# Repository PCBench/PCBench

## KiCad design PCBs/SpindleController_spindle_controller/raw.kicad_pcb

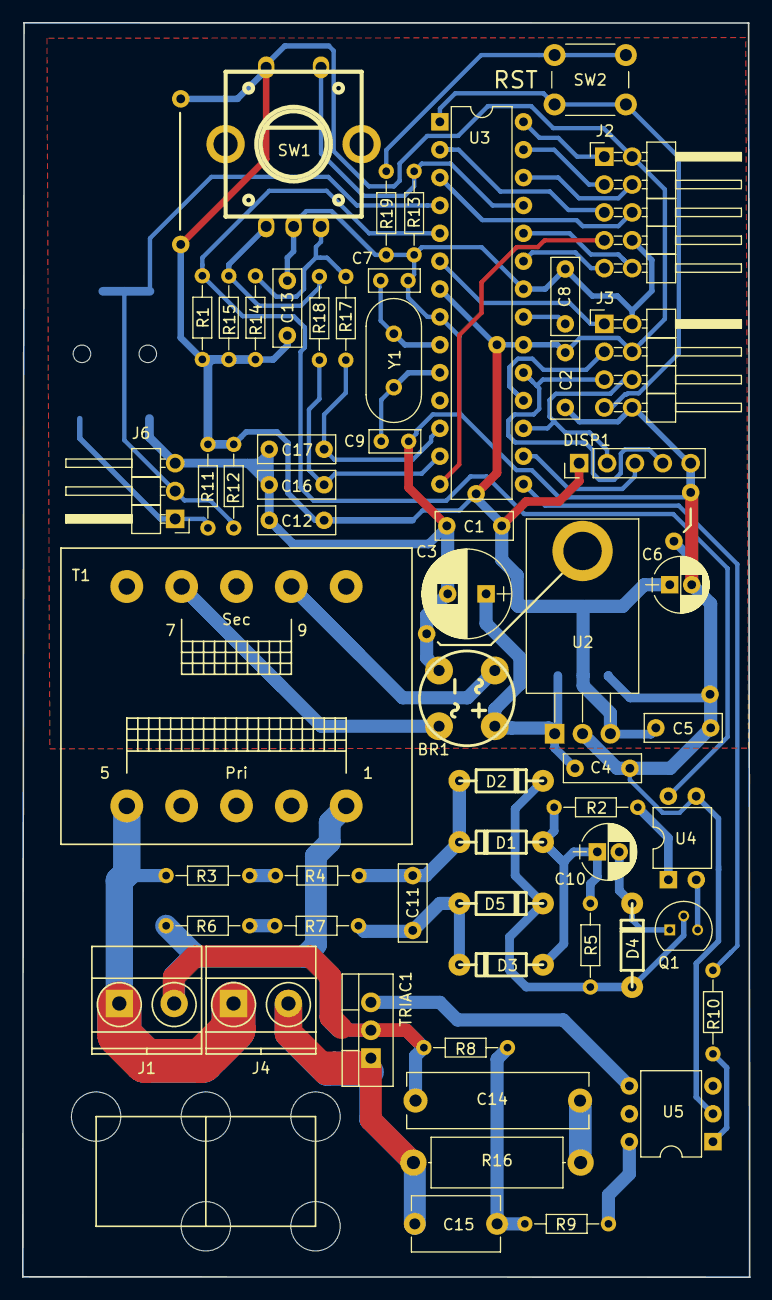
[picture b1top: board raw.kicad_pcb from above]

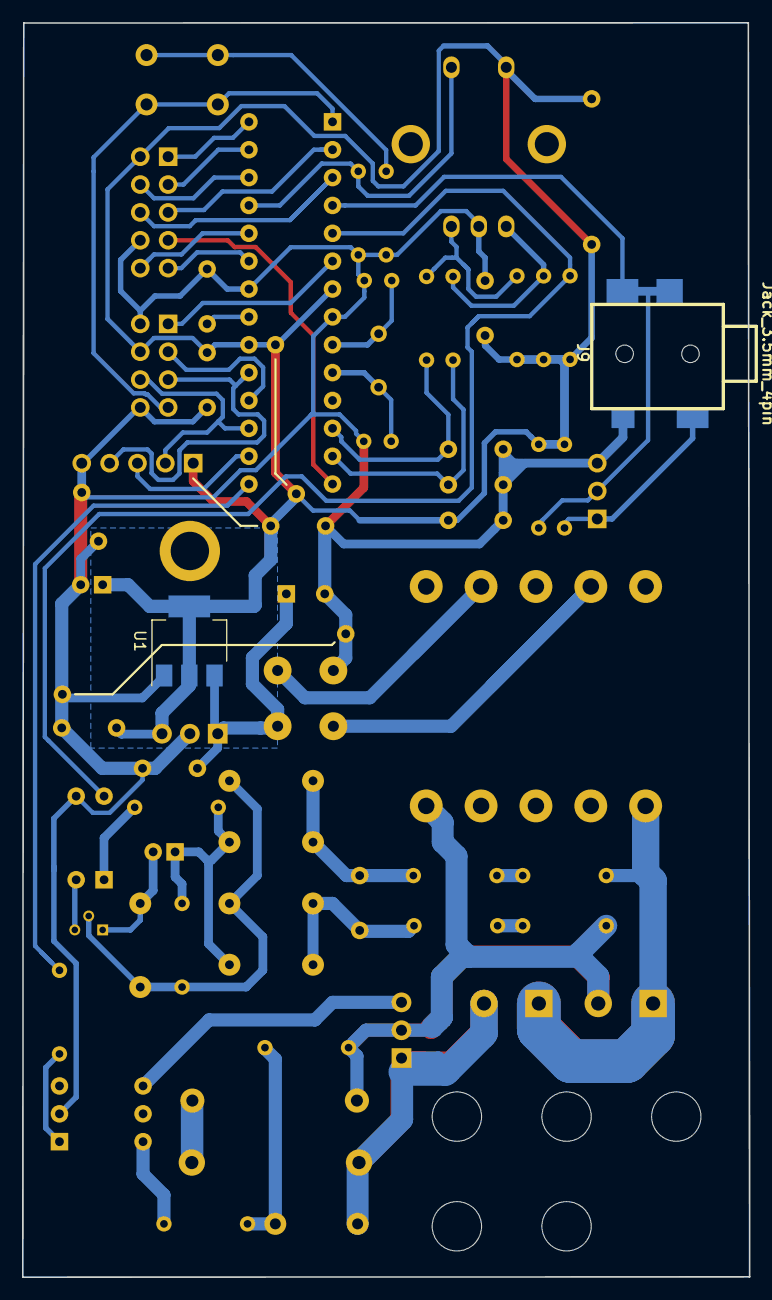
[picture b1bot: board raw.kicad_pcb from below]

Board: 2 copper layers, 66.3 x 114.4 mm, 69 parts (2 on the bottom side), 49 nets.

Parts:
BR1: D_Bridge_+AA-; bridge_wob
C1, C2, C5, C8, C12, C13: 100n; C_Rect_L7.0mm_W2.5mm_P5.00mm
C3: 220u; CP_Radial_D8.0mm_P3.50mm
C4: 470n; C_Rect_L7.0mm_W2.5mm_P5.00mm
C6: 100u; CP_Radial_D5.0mm_P2.00mm
C7, C9: 27p; C_Rect_L4.6mm_W2.0mm_P2.50mm_MKS02_FKP02
C10: 10u; CP_Radial_D5.0mm_P2.00mm
C11: 1n; C_Rect_L7.0mm_W2.5mm_P5.00mm
C14: 10n; C_Rect_L16.5mm_W5.0mm_P15.00mm_MKT
C15: 1n; C_Disc_D8.0mm_W5.0mm_P7.50mm
C16, C17: 47n; C_Rect_L7.0mm_W2.5mm_P5.00mm
D1, D2, D3, D4, D5: 1N4841; diode_do35
DISP1: 8x7SEG; Pin_Header_Straight_1x05_Pitch2.54mm
J1: VAC 230V; TerminalBlock_Pheonix_MKDS1.5-2pol
J2: AUX/CONTROL; Pin_Header_Angled_2x05_Pitch2.54mm
J3: ICP; Pin_Header_Angled_2x04_Pitch2.54mm
J4: Load output; TerminalBlock_Pheonix_MKDS1.5-2pol
J6: CONN_01X03; Pin_Header_Angled_1x03_Pitch2.54mm
J7, J7#2, J7#3, J7#4: GND_JUMPER; JUMPER_PIN
J8, J8#2, J8#3, J8#4: VCC_JUMPER; JUMPER_PIN
J9: Jack_3.5mm_4pin; jack_3.5_sj1-3514-smt
Q1: 2N3904; TO-92_Molded_Narrow
R1, R12, R13, R14, R15: 10k; R_Axial_DIN0204_L3.6mm_D1.6mm_P7.62mm_Horizontal
R2, R10: 1k; R_Axial_DIN0204_L3.6mm_D1.6mm_P7.62mm_Horizontal
R3, R6: 120k; R_Axial_DIN0204_L3.6mm_D1.6mm_P7.62mm_Horizontal
R4, R7: 220k; R_Axial_DIN0204_L3.6mm_D1.6mm_P7.62mm_Horizontal
R5: 33k; R_Axial_DIN0204_L3.6mm_D1.6mm_P7.62mm_Horizontal
R8: 470; R_Axial_DIN0204_L3.6mm_D1.6mm_P7.62mm_Horizontal
R9, R19: 360; R_Axial_DIN0204_L3.6mm_D1.6mm_P7.62mm_Horizontal
R11: 220; R_Axial_DIN0204_L3.6mm_D1.6mm_P7.62mm_Horizontal
R16: 47; R_Axial_DIN0414_L11.9mm_D4.5mm_P15.24mm_Horizontal
R17, R18: 2k2; R_Axial_DIN0204_L3.6mm_D1.6mm_P7.62mm_Horizontal
SW1: Rotary_Encoder_Switch; encoder_alps-ec12d
SW2: SW_SPST; SW_PUSH_6mm
T1: 230 - 6VAC (Spitznagel SPK 01406); Trafo_CHK-EI30-2VA_1xSec
TRIAC1: BT138; TO-220_Vertical
U1: LT1117-5; SOT-223
U2: LM2940CT-5.0; TO-220_Horizontal_connected_tab
U3: ATMEGA328P-PU; DIP-28_W7.62mm
U4: PC817; DIP-4_W7.62mm
U5: MOC3020M; DIP-6_W7.62mm
WIRESTRAP1: 2x Ziplock wire strap; WireStrap_2X_5HOLES
Y1: 16MHz; Crystal_HC49-U_Vertical

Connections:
/DBG: J3.1, U3.6
/MISO: J3.3, U3.18
/MOSI: DISP1.2, J3.6, U3.17
/PB0: J2.7, U3.14
/PC3: J2.4, U3.26
/PD6: J2.9, U3.23
/PD7: J2.10, U3.24
/RENC_A: C16.2, R18.2, U3.13
/RENC_B: C17.2, R17.2, U3.12
/ROT_PULSE: J6.2, J9.2, J9.3, R12.1, U3.4
/RST: J3.7, SW2.1, U3.1
/RX: J2.5, U3.2
/SCK: DISP1.4, J3.5, U3.19
/SCL: J2.1, U3.28
/SDA: J2.3, U3.27
/SEG_CS: DISP1.3, U3.16
/SW1: R13.2, SW1.4, U3.25
/TRIAC_DRIVE: R10.1, U3.15
/TX: J2.6, U3.3
/VAC_L: C14.1, J1.2, R6.2, R8.2, T1.1, TRIAC1.2
/VAC_N: J1.1, J4.1, R3.2, T1.5
/ZCROSS_PULSE: R1.1, U3.5, U4.4
GND: BR1.4, C1.2, C2.1, C3.2, C4.2, C5.2, C6.2, C7.2, C8.2, C9.2, C12.2, C13.1, C16.1, C17.1, DISP1.5, J2.8, J3.2, J3.8, J6.3, J7.1, J7#2.1, J7#3.1, J7#4.1, J9.4, R13.1, R19.2, SW1.2, U1.1, U2.2, U3.8, U3.22, U4.3, U5.2
unnamed: BR1.1, C3.1, C4.1, U1.3, U2.1
unnamed: BR1.2, T1.9
unnamed: BR1.3, T1.7
unnamed: C7.1, U3.9, Y1.1
unnamed: C8.1, U3.21
unnamed: C9.1, U3.10, Y1.2
unnamed: C10.1, D1.1, D3.1, R2.2, R5.2
unnamed: C10.2, D4.2, Q1.1
unnamed: C11.1, D1.2, D2.1, R4.1
unnamed: C11.2, D3.2, D5.1, R7.1
unnamed: C14.2, R16.2
unnamed: C15.1, R8.1, R9.2
unnamed: C15.2, J4.2, R16.1, TRIAC1.1
unnamed: D2.2, D4.1, D5.2, Q1.2, R5.1
unnamed: J6.1, J9.1, R11.2
unnamed: Q1.3, U4.2
unnamed: R2.1, U4.1
unnamed: R3.1, R4.2
unnamed: R6.1, R7.2
unnamed: R9.1, U5.6
unnamed: R10.2, U5.1
unnamed: R14.1, R17.1, SW1.3
unnamed: R15.1, R18.1, SW1.1
unnamed: R19.1, SW2.2
unnamed: TRIAC1.3, U5.4
VCC: C1.1, C2.2, C5.1, C6.1, C12.1, C13.2, DISP1.1, J2.2, J3.4, J8.1, J8#2.1, J8#3.1, J8#4.1, R1.2, R11.1, R12.2, R14.2, R15.2, SW1.5, U1.2, U1.4, U2.3, U3.7, U3.20

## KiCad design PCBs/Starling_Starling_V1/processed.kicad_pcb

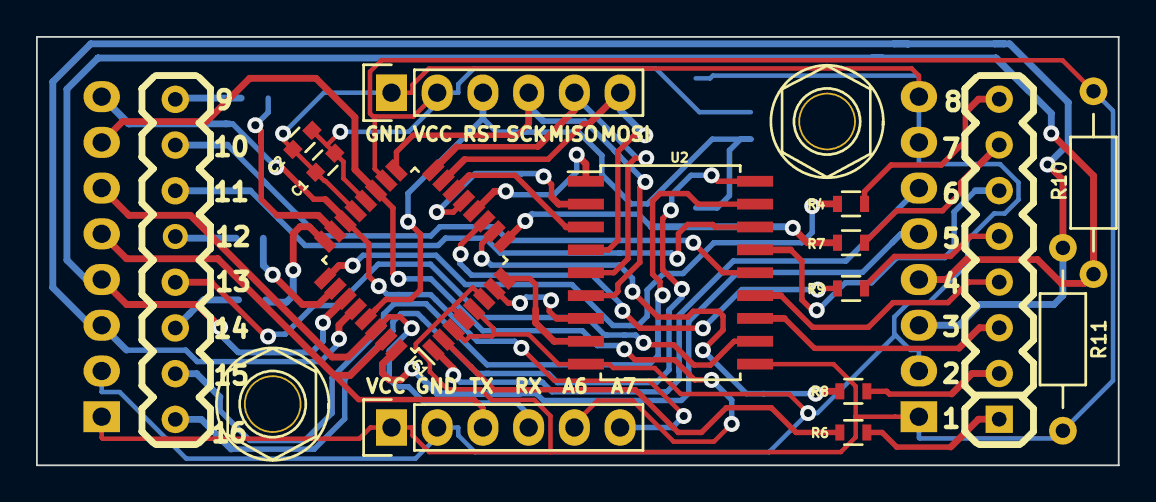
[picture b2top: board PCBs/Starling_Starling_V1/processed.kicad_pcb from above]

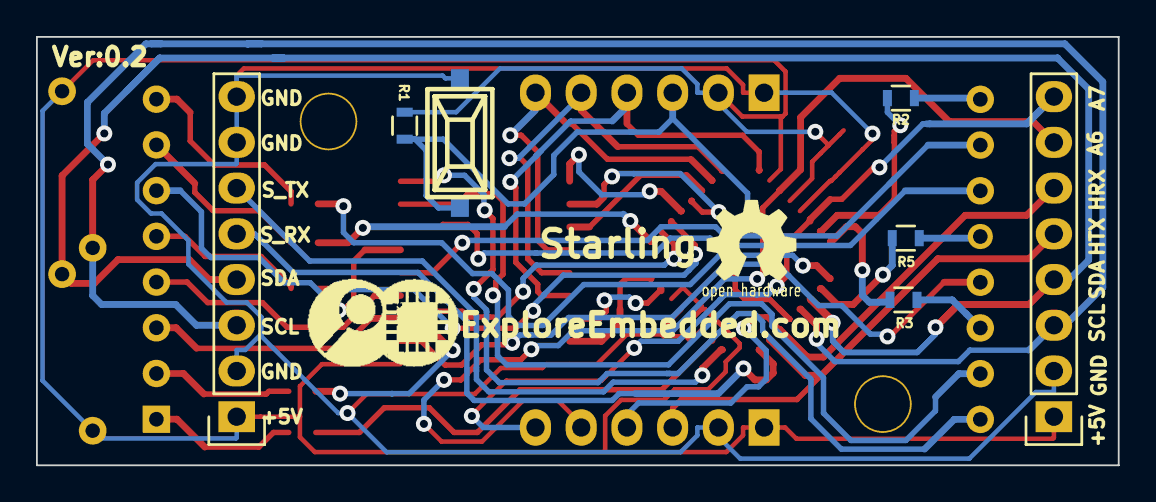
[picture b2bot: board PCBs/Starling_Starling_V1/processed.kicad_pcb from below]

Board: 2 copper layers, 60.1 x 23.8 mm, 24 parts (8 on the bottom side), 43 nets.

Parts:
C1, C2: 0.1uF; C_0603
IC1: ATMEGA8-AI; LQFP-32_7x7mm_Pitch0.8mm
LOGO: LOGO (2)
P1, P2: CONN_01X01; M3_mounting
P3, P6: CONN_01X06; Pin_Header_Straight_1x06
P4, P5: CONN_01X08; Pin_Header_Straight_1x08
R1: 10K; R_0603
R2, R3, R4, R5, R6, R7, R8, R9: 22r; R_0603
R10, R11: 10K; Resistor_Horizontal_RM10mm
SW1: SPST; smd_push
U1: 8x8_Row_anode; 8X8_matrix_2.3inch
U2: ULN2803; SOIC-18_7.5x11.6mm_Pitch1.27mm

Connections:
+5C: C1.1, C2.1, IC1.4, IC1.6, IC1.18, IC1.20, P3.2, P4.1, P5.1, P6.1, R1.1, R10.1, R11.1, U2.10
/ADC6: IC1.19, P4.7, P6.5
/ADC7: IC1.22, P4.8, P6.6
/H_RX: IC1.30, P4.6, P6.4
/H_TX: IC1.31, P4.5, P6.3
/MISO: IC1.16, P3.5, U2.5
/MOSI: IC1.15, P3.6, U2.4
/PB6: IC1.7, U2.7
/PB7: IC1.8, U2.8
/RST: IC1.29, P3.3, R1.2, SW1.2
/SCK: IC1.17, P3.4, U2.6
/SCL: IC1.28, P4.3, P5.3, R11.2
/SDA: IC1.27, P4.4, P5.4, R10.2
/S_RX: IC1.32, P5.5
/S_TX: IC1.1, P5.6
GND: C1.2, C2.2, IC1.3, IC1.5, IC1.21, P3.1, P4.2, P5.2, P5.7, P5.8, P6.2, SW1.1, U2.9
unnamed: IC1.2, R6.2
unnamed: IC1.9, R7.2
unnamed: IC1.10, R8.2
unnamed: IC1.11, R9.2
unnamed: IC1.12, U2.1
unnamed: IC1.13, U2.2
unnamed: IC1.14, U2.3
unnamed: IC1.23, R2.2
unnamed: IC1.24, R3.2
unnamed: IC1.25, R4.2
unnamed: IC1.26, R5.2
unnamed: R2.1, U1.9
unnamed: R3.1, U1.14
unnamed: R4.1, U1.8
unnamed: R5.1, U1.12
unnamed: R6.1, U1.1
unnamed: R7.1, U1.7
unnamed: R8.1, U1.2
unnamed: R9.1, U1.5
unnamed: U1.3, U2.12
unnamed: U1.4, U2.13
unnamed: U1.6, U2.15
unnamed: U1.10, U2.14
unnamed: U1.11, U2.16
unnamed: U1.13, U2.11
unnamed: U1.15, U2.17
unnamed: U1.16, U2.18

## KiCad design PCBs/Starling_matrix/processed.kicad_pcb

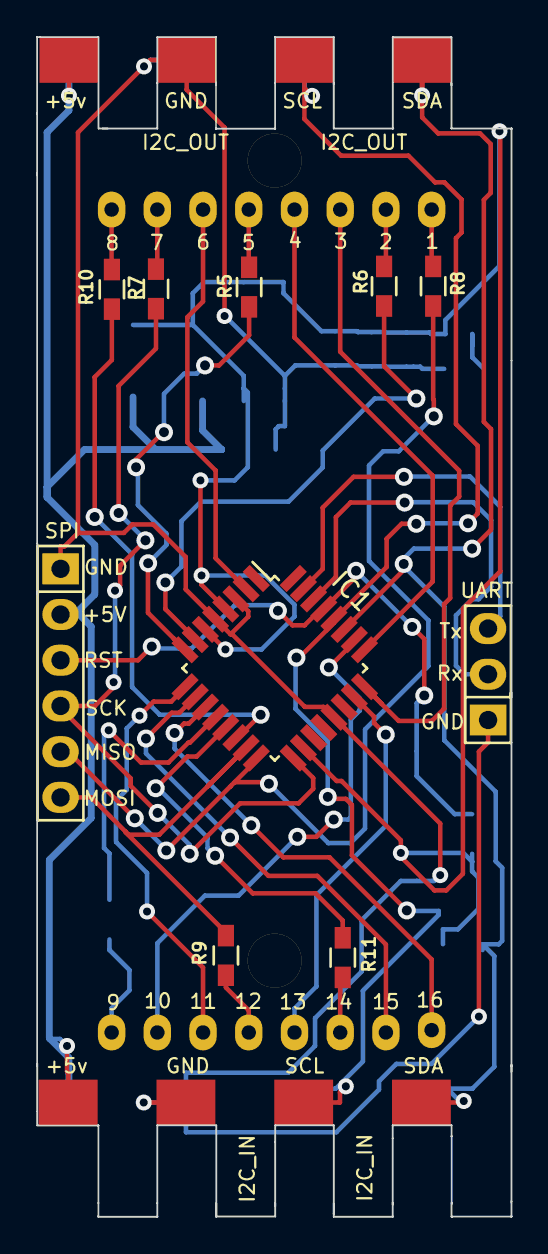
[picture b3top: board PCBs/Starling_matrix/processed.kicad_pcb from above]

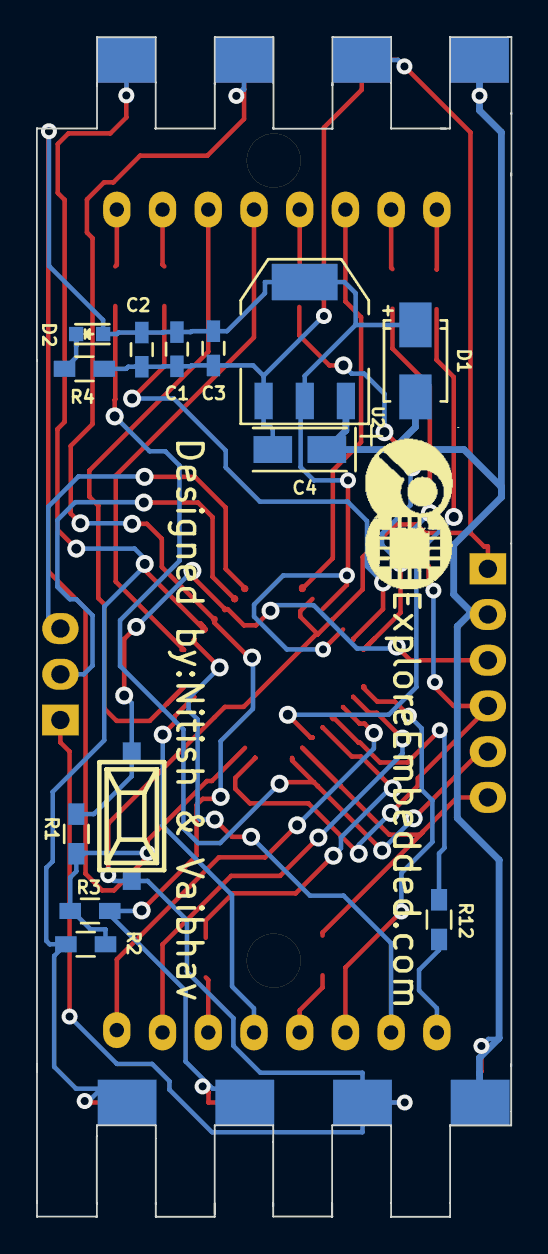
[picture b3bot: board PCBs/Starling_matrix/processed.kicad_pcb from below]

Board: 2 copper layers, 26.4 x 65.6 mm, 29 parts (14 on the bottom side), 33 nets.

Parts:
C1, C2, C3: 0.1uf; C_0603_HandSoldering
C4: 10uF; TantalC_SizeA_EIA-3216_Wave
D1: DIODE; SMA_Standard
D2: LED; LED-0603
IC1: ATMEGA8-AI; TQFP-32_7x7mm_Pitch0.8mm
LOGO: LOGO (2)
P1: CONN_01X06; Pin_Header_Straight_1x06
P2, P3: CONN_01X04; matrix_connector
P4: CONN_01X03; Pin_Header_Straight_1x03
P5, P6: CONN_01X01; 1pin
R1, R2, R3: 10K; R_0603_HandSoldering
R4: 470E; R_0603_HandSoldering
R5, R6, R7, R8, R9, R10, R11, R12: 22E; R_0603_HandSoldering
SW1: SPST; smd_push
U1: DispHB2388; 8x8dot matrix
U2: lm1117/3.3; lm117_SOT-223

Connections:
+3V3: C1.1, C2.1, C3.1, D1.1, D2.1, IC1.4, IC1.6, IC1.18, R1.1, R2.1, R3.1, U2.2, U2.4
+5V: C4.1, D1.2, P1.2, P2.1, P3.1, U2.3
/MISO: IC1.16, P1.5, R8.1
/MOSI: IC1.15, P1.6, R9.1
/PB6: IC1.7, R6.1
/PB7: IC1.8, R5.1
/RST: IC1.29, P1.3, R1.2, SW1.2
/Rx: IC1.30, P4.2
/SCK: IC1.17, P1.4, R7.1
/SCL: IC1.28, P2.3, P3.3, R3.2
/SDA: IC1.27, P2.4, P3.4, R2.2
/Tx: IC1.31, P4.3
GND: C1.2, C2.2, C3.2, C4.2, IC1.3, IC1.5, IC1.21, P1.1, P2.2, P3.2, P4.1, R4.2, SW1.1, U2.1
unnamed: D2.2, R4.1
unnamed: IC1.2, U1.6
unnamed: IC1.9, U1.11
unnamed: IC1.10, U1.15
unnamed: IC1.11, U1.16
unnamed: IC1.12, R12.1
unnamed: IC1.13, R11.1
unnamed: IC1.14, R10.1
unnamed: IC1.23, U1.13
unnamed: IC1.24, U1.3
unnamed: IC1.25, U1.4
unnamed: IC1.26, U1.10
unnamed: R5.2, U1.5
unnamed: R6.2, U1.2
unnamed: R7.2, U1.7
unnamed: R8.2, U1.1
unnamed: R9.2, U1.12
unnamed: R10.2, U1.8
unnamed: R11.2, U1.14
unnamed: R12.2, U1.9

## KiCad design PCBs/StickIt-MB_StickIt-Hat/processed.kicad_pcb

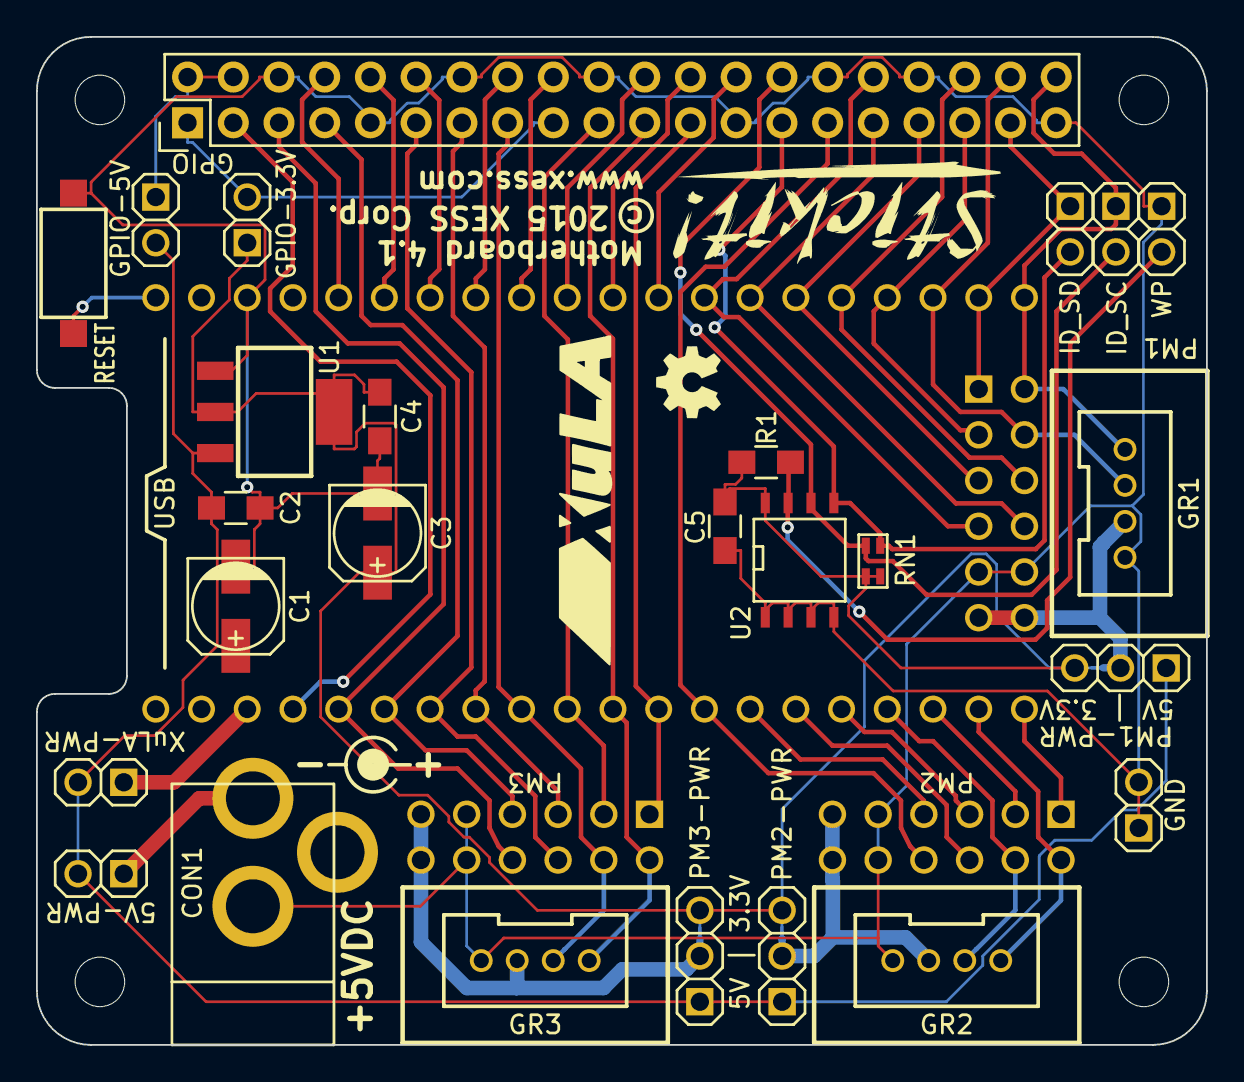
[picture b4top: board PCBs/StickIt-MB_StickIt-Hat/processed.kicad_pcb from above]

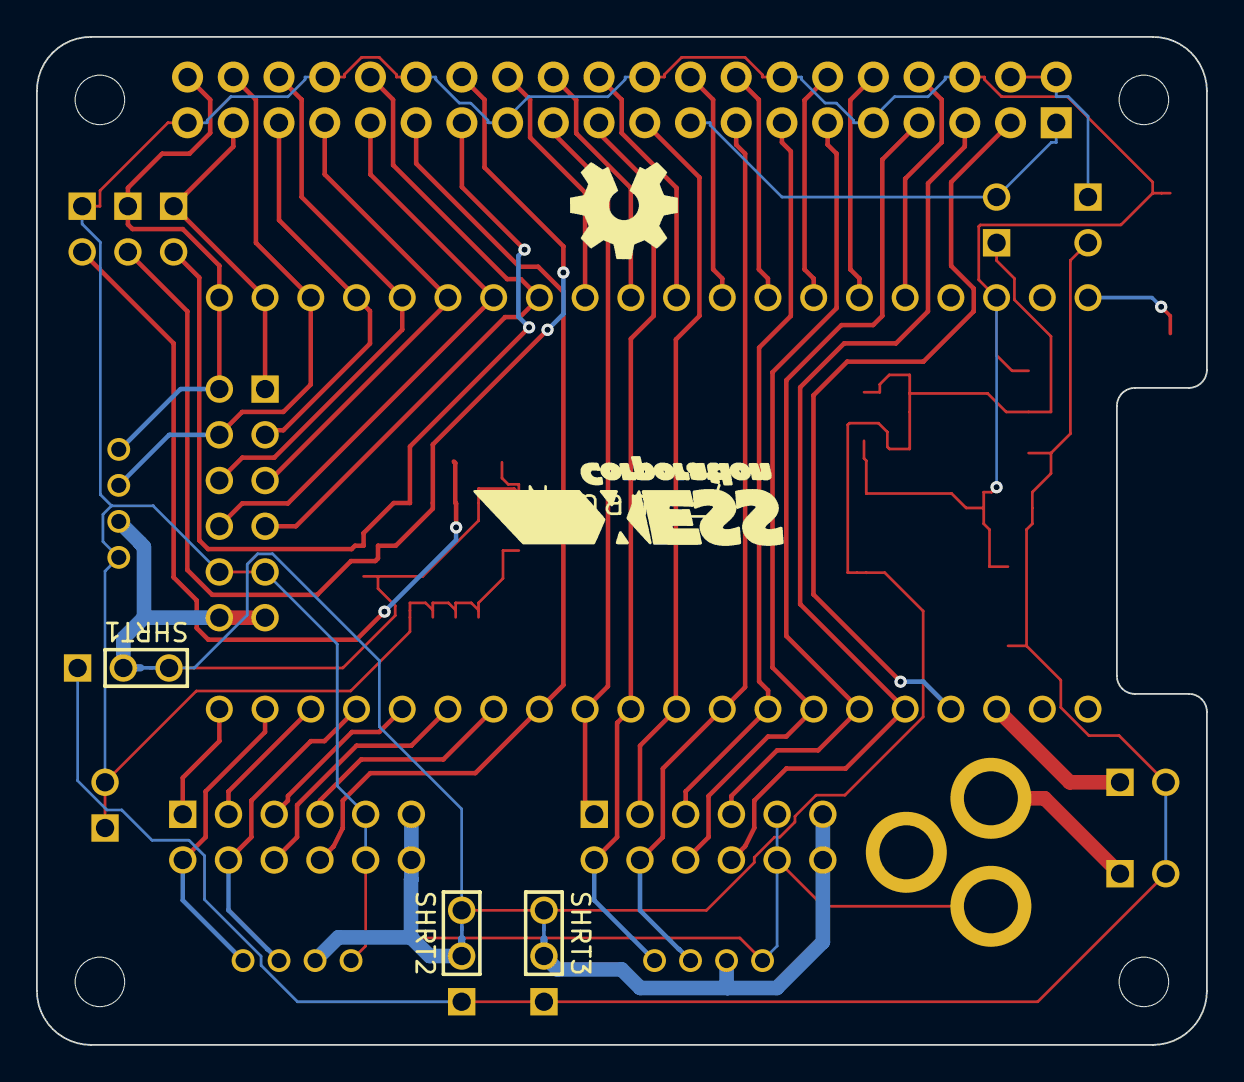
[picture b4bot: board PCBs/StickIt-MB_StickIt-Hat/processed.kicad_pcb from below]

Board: 2 copper layers, 65.0 x 56.0 mm, 41 parts (5 on the bottom side), 47 nets.

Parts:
C1, C3: 22uF; c_elec_5x5.3
C2, C4: 4.7uF; R_0805_HandSoldering
C5: 0.1uF; R_0805_HandSoldering
CON1: BARREL_JACK
GPIO1: RPi_GPIO; Pin_Header_Straight_2x20
GR1, GR2, GR3: Grove; GROVE_MALE
J1: XuLA_IO_HDR; XuLA_IO_Hdr
J3, J4, J5: JSHORTNORMAL; xess-JSHORT
JP1, JP2, JP3: JUMPER3; HDR_1x3
JP4, JP5, JP6, JP7, JP8, JP9, JP10: JUMPER; HDR_1x2
Noname_1: oshw_logo_4mm
Noname_2: stickit_logo_18mm
Noname_3: oshw_logo_6mm
Noname_4: xesscorp2
Noname_5, Noname_6, Noname_7, Noname_8: RPi_Hat_Mounting_Hole
PM1, PM2, PM3: PMOD_SCKT-12
R1: 1K; R_0805_HandSoldering
RN1: 3.9K; CTS_742C043
SW1: SW_PUSH; RS-282G05A3-SM_RT
TP1: JUMPER; HDR_1x2
U1: NCV1117; SOT-223
U2: CAT24C32; SOIC-8-N

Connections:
+3.3V: C3.1, C4.1, C5.1, J3.2, J4.2, J5.2, JP1.3, JP2.3, JP3.3, JP7.1, R1.1, RN1.1, RN1.2, U1.2, U1.4, U2.8
+3.3V-RPi: GPIO1.1, GPIO1.17, JP7.2
+5V: C1.1, C2.1, JP1.1, JP2.1, JP3.1, JP4.2, JP5.2, JP6.2, U1.3
+5V-RPi: GPIO1.2, GPIO1.4, JP4.1
+5V-XuLA: J1.3, JP5.1
CHAN0: GPIO1.37, J1.22, JP10.1, PM1.1
CHAN1: GPIO1.38, GR1.2, J1.23, PM1.8
CHAN2: GPIO1.35, J1.24, PM1.2
CHAN3: GPIO1.36, J1.25, PM1.9
CHAN4: GPIO1.33, J1.26, PM1.3
CHAN5: GPIO1.31, J1.27, PM1.10
CHAN6: GPIO1.32, J1.28, PM1.4
CHAN7: GPIO1.26, J1.29
CHAN8: GPIO1.24, J1.30
CHAN9: GPIO1.22, J1.31
CHAN10: GPIO1.18, J1.32
CHAN11: GPIO1.16, J1.33
CHAN12: GPIO1.12, J1.34
CHAN13: GPIO1.10, J1.35
CHAN14: GPIO1.8, J1.36
CHAN15: J1.20, PM2.1
CHAN16: GR2.1, J1.19, PM2.7
CHAN17: J1.18, PM2.2
CHAN18: GR2.2, J1.17, PM2.8
CHAN19: J1.16, PM2.3
CHAN20: J1.15, PM2.9
CHAN21: J1.14, PM2.4
CHAN22: GPIO1.29, J1.13, PM2.10
CHAN23: GPIO1.23, J1.12, PM3.1
CHAN24: GPIO1.21, GR3.1, J1.11, PM3.7
CHAN25: GPIO1.19, J1.10, PM3.2
CHAN26: GPIO1.15, GR3.2, J1.9, PM3.8
CHAN27: GPIO1.13, J1.8, PM3.3
CHAN28: GPIO1.11, J1.7, PM3.9
CHAN29: GPIO1.7, J1.6, PM3.4
CHAN30: GPIO1.5, J1.5, PM3.10
CHAN31: GPIO1.3, J1.4
CHANCLK: GPIO1.40, GR1.1, J1.21, JP9.1, PM1.7
GND: C1.2, C2.2, C3.2, C4.2, C5.2, CON1.2, GPIO1.6, GPIO1.9, GPIO1.14, GPIO1.20, GPIO1.25, GPIO1.30, GPIO1.34, GPIO1.39, GR1.4, GR2.4, GR3.4, J1.38, JP8.1, PM1.5, PM1.11, PM2.5, PM2.11, PM3.5, PM3.11, SW1.2, TP1.1, TP1.2, U1.1, U2.1, U2.2, U2.3, U2.4
ID_SC: GPIO1.28, JP9.2, RN1.4, U2.6
ID_SD: GPIO1.27, JP10.2, RN1.3, U2.5
unnamed: CON1.1, JP6.1
unnamed: GR1.3, J3.1, JP1.2, PM1.6, PM1.12
unnamed: GR2.3, J4.1, JP2.2, PM2.6, PM2.12
unnamed: GR3.3, J5.1, JP3.2, PM3.6, PM3.12
unnamed: J1.40, SW1.1
unnamed: JP8.2, R1.2, U2.7

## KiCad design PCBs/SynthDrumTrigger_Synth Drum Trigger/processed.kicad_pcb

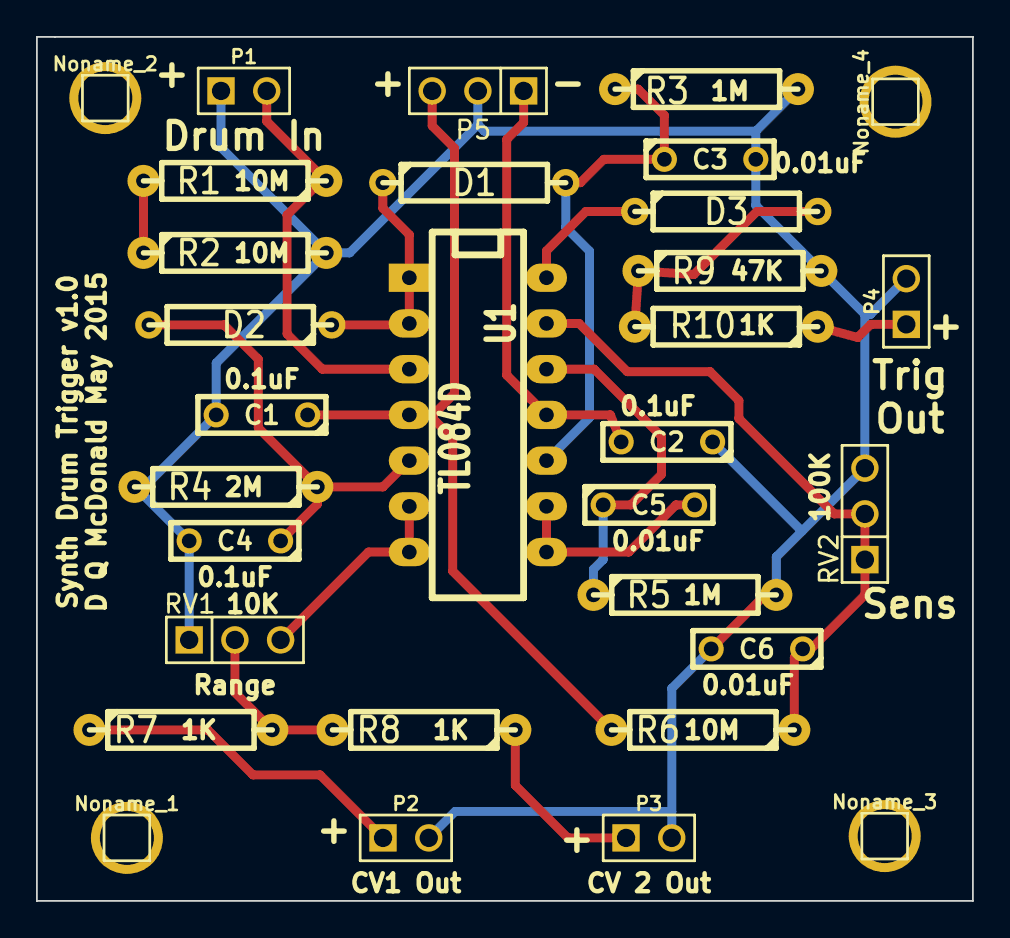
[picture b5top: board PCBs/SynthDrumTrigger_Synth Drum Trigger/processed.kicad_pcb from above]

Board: 2 copper layers, 52.0 x 48.0 mm, 31 parts (0 on the bottom side), 18 nets.

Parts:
C1, C2, C4: 0.1uF; C2
C3, C6: 0.01uF; C2
C5: 0.01; C2
D1, D2, D3: DIODE; R4
Noname_1, Noname_2, Noname_3, Noname_4: Val**; PIN_ARRAY_1
P1, P2, P3, P4: CONN_2; PIN_ARRAY_2X1
P5: Power_In; PIN_ARRAY_3X1
R1, R2, R6: 10M; R4-LARGE_PADS
R3, R5: 1M; R4-LARGE_PADS
R4: 2M; R4-LARGE_PADS
R7, R8, R10: 1K; R4-LARGE_PADS
R9: 47K; R4-LARGE_PADS
RV1: 10K; PIN_ARRAY_3X1
RV2: 100K; PIN_ARRAY_3X1
U1: TL084D; DIP-14__300_ELL

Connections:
+12V: C1.1, P5.3, R6.2, U1.4
-12V: C2.2, P5.1, U1.11
GND: C1.2, C2.1, C3.2, C4.2, C6.2, P1.1, P2.2, P3.2, P4.2, P5.2, R2.2, R3.2, R4.2, R5.2, R9.2, RV1.1, RV2.3
unnamed: C3.1, D1.2, R3.1, U1.10
unnamed: C4.1, D2.2, R4.1, U1.5
unnamed: C5.1, R5.1, U1.12
unnamed: C5.2, U1.8, U1.9
unnamed: C6.1, R6.1, RV2.1, RV2.2, U1.13
unnamed: D1.1, D2.1, U1.1, U1.2
unnamed: D3.1, U1.14
unnamed: D3.2, R9.1, R10.2
unnamed: P1.2, R1.1, U1.3
unnamed: P2.1, R7.1
unnamed: P3.1, R8.1
unnamed: P4.1, R10.1
unnamed: R1.2, R2.1
unnamed: R7.2, R8.2, RV1.2
unnamed: RV1.3, U1.6, U1.7

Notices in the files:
PCBs/StickIt-MB_StickIt-Hat/processed.kicad_pcb:
(c) 2015
